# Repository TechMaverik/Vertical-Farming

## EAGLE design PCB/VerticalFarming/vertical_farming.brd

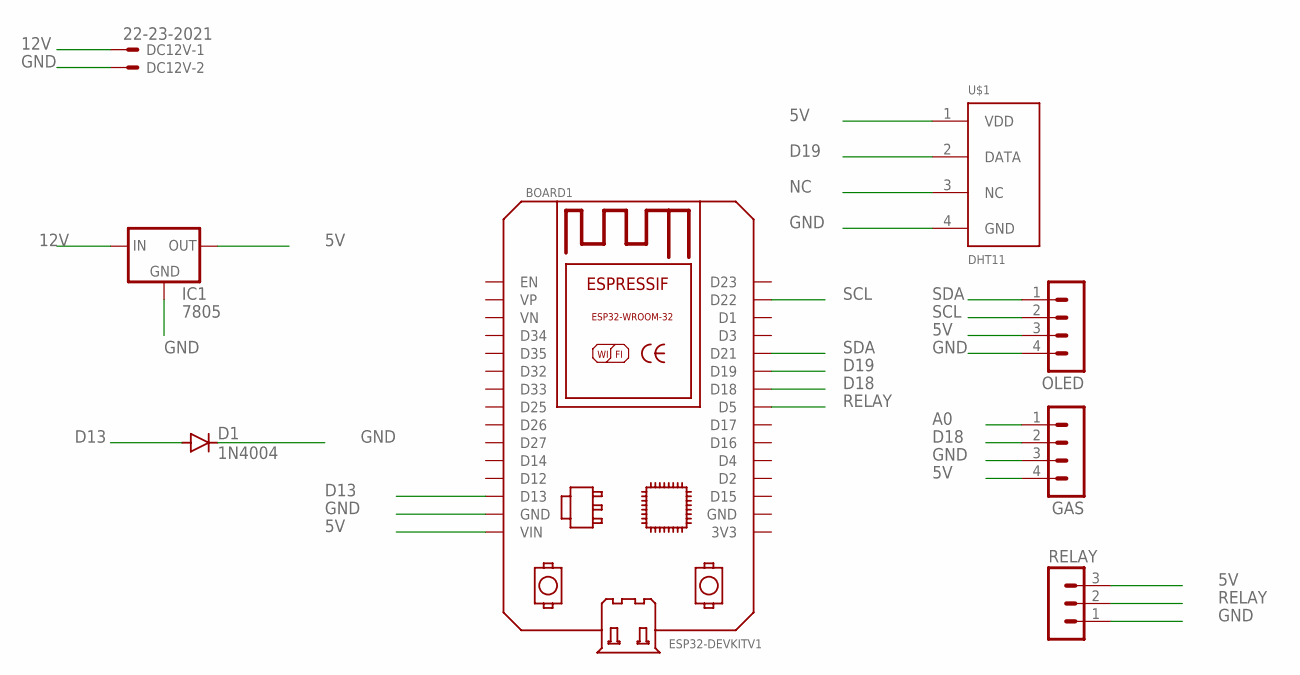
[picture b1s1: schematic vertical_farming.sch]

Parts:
BOARD1: ESP32DEVKITV1; ESP32-DEVKITV1
D1: 1N4004; DO41-10
DC12V: 22-23-2021
GAS: MA04-1
IC1: 7805; 78XXL
OLED: MA04-1
RELAY: MA03-1
U$1: DHT11

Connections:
5V: BOARD1.VIN, GAS.4, IC1.OUT, OLED.3, RELAY.3, U$1.1 (VDD)
12V: DC12V.1, IC1.IN
A0: GAS.1
D13: BOARD1.D13, D1.A
D18: BOARD1.D18, GAS.2
D19: BOARD1.D19, U$1.2 (DATA)
GND: BOARD1.GND, D1.C, DC12V.2, GAS.3, IC1.GND, OLED.4, RELAY.1, U$1.4 (GND)
NC: U$1.3 (NC)
RELAY: BOARD1.D5, RELAY.2
SCL: BOARD1.D22, OLED.2
SDA: BOARD1.D21, OLED.1

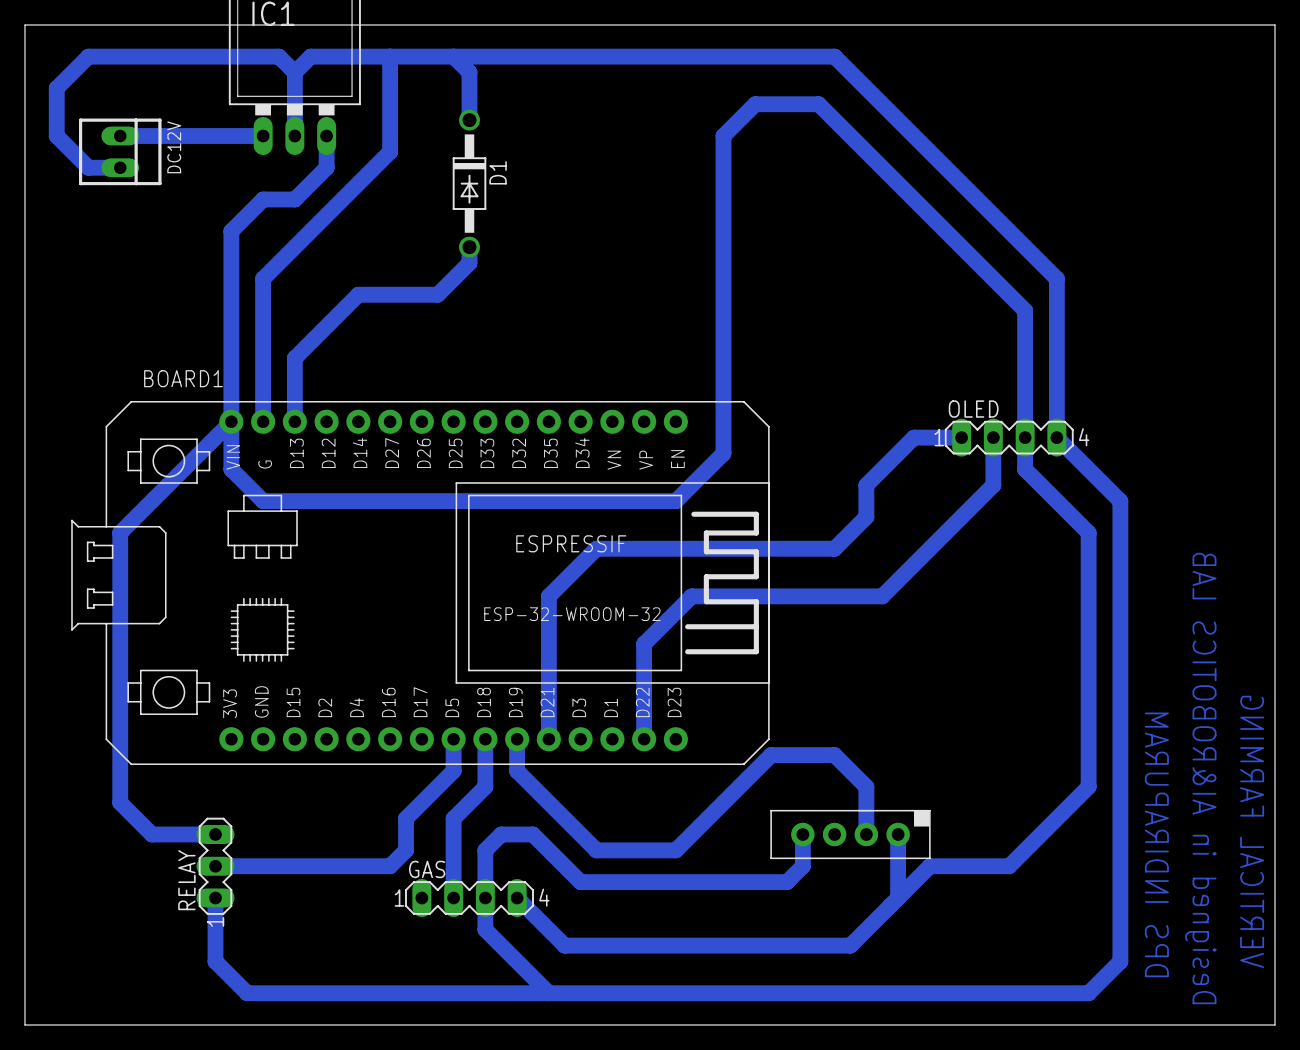
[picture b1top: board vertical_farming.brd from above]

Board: 2 copper layers, 100.0 x 80.0 mm, 8 parts (0 on the bottom side), 9 nets.

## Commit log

2025-08-26 pcb designing
2025-09-01 base framework commit
2025-09-02 base functionality done
2025-09-02 code updates
2025-09-03 Dont change main.cpp
2025-09-03 base code update
2025-09-03 remove unwanted files
2025-09-08 Added Requirements
2025-09-08 Added auto refreshing options
